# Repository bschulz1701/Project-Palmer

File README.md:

# Project-Palmer
Multiple system designs for golf course turf monitoring project

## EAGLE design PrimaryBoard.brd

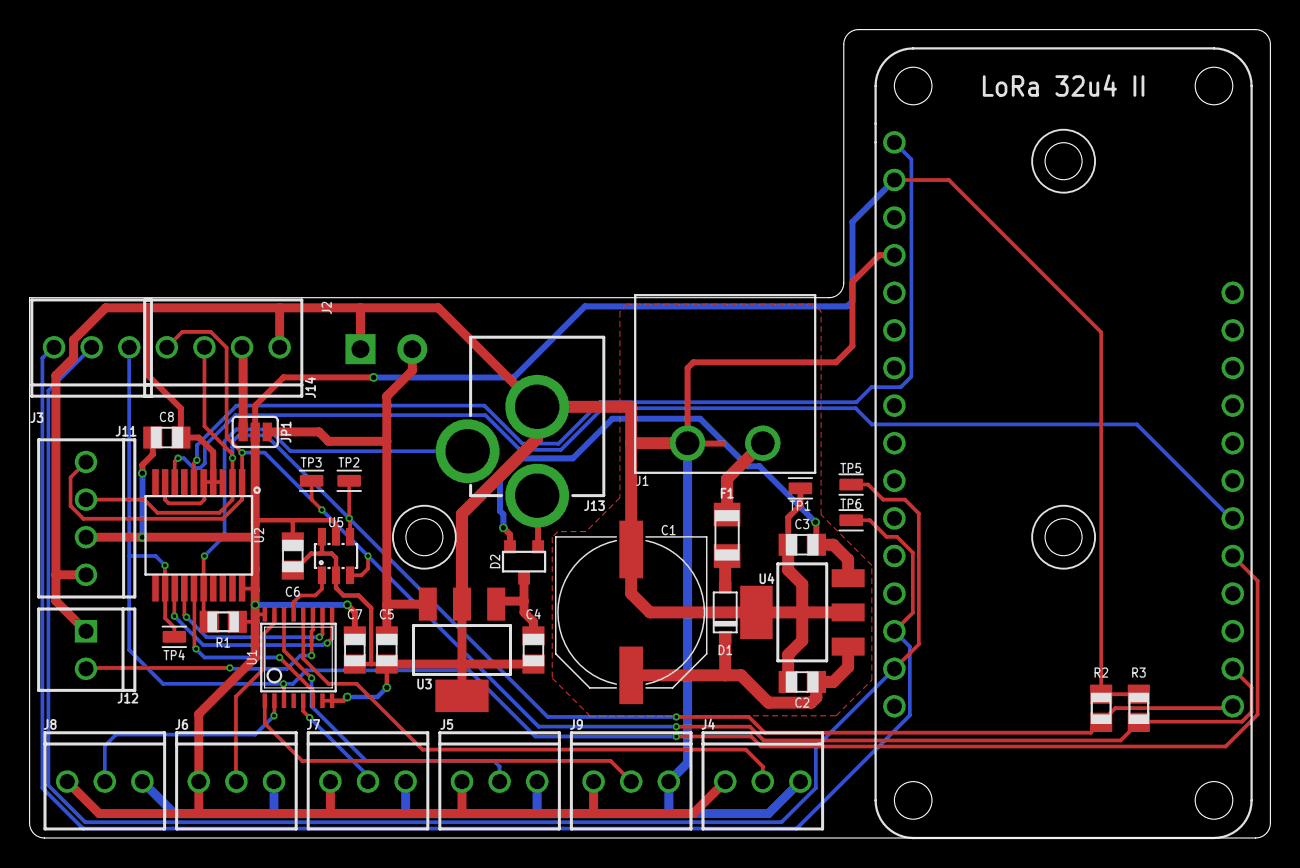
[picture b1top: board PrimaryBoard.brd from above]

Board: 2 copper layers, 83.8 x 54.6 mm, 43 parts (0 on the bottom side), 29 nets.

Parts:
C1: 1000uF; PANASONIC_G
C2: 0.33uF; C0805
C3, C6, C7, C8: 0.1uF; C0805
C4, C5: 1uF; C0805
D1: SOD-123
D2: DIODE_CCSDM40E20LCSOT23; SOT23-3
F1: 50/150mA; 1206
H1, H2, H3: 2_56
J1: 1X02_39532_RIGHT
J2: SCREWTERMINAL-3.5MM-2-NS
J3, J4, J5, J6, J7, J8, J9: CONN_32.54_SCREW; 1X03_SCREW
J10: LORA32U4II
J11, J14: CONN_42.54_SCREW; 1X04_SCREW
J12: 1X02_2.54_SCREWTERM
J13: POWER_JACK; POWER_JACK_PTH
JP1: JUMPER-SMT_3_1-NC_PASTE_SILK; SMT-JUMPER_3_1-NC_PASTE_SILK
R1: 100k; R0805
R2, R3: 10k; R0805
TP1, TP2, TP3, TP4, TP5, TP6: TESTPOINTRCU; TESTPOINT_0603
U1: CD74HC4052PW; TSSOP16
U2: MCP23008SSOP; SSOP20
U3: TC1262-3.3V; SOT223
U4: UA78M05SOT223; SOT223
U5: MCP3421A3; SOT23-6L

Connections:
3V3_CORE: C6.1, C7.1, C8.1, J4.3, J5.3, J6.3, J7.3, J8.3, J9.3, J10.3V3, J11.2, JP1.2, R1.2, R2.2, R3.2, U1.16, U2.20, U5.5
3V3_EXT: J14.3, JP1.1
3V3_MAIN: C5.1, J2.2, JP1.3, U3.3
5V: C3.1, D2.2, U4.3
5V_CORE: C4.1, D2.3, U3.1
5V_EXT: D2.1, J13.PWR
5V_EXT_SENSE: J13.GNDBREAK, R1.1, U2.16
24V_AC: F1.1, J1.2
A0: J4.2, U1.12
A1: J5.2, U1.14
A2: J6.2, U1.15
A3: J12.P1, U1.11
A_COM: U1.13, U5.1
GND: C1.-, C2.2, C3.2, C4.2, C5.2, C6.2, C7.2, C8.2, J1.1, J2.1, J4.1, J5.1, J6.1, J7.1, J8.1, J9.1, J10.GND, J11.1, J12.P2, J13.GND, J14.4, TP1.1, U1.7, U1.8, U2.3, U2.4, U2.5, U2.9, U3.2, U3.4, U4.2, U4.4, U5.2, U5.6
IO_EN: U1.6, U2.15
IO_INT: J10.30, U2.8
unnamed: D1.ANODE, F1.2
ONEWIRE: J3.3, J10.29, TP4.1, U1.3, U2.12
OW0: J9.2, U1.1
OW1: J7.2, U1.5
OW2: J8.2, U1.2
RESET: J10.RST, U2.6
RX: J3.1, J10.20, TP6.1
S0: U1.10, U2.14
S1: U1.9, U2.13
SCL: J10.18, J11.4, J14.1, R3.1, TP3.1, U2.1, U5.3
SDA: J10.19, J11.3, J14.2, R2.1, TP2.1, U2.2, U5.4
TX: J3.2, J10.21, TP5.1
V_RECT: C1.+, C2.1, D1.CAT, U4.1

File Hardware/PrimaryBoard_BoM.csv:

"Qty","Value","Device","Package","Parts","Description","DIGIKEY","DISP","MF","MPN","PROD_ID","SPICEPREFIX","VALUE",
"1","","CONN_022.54_SCREW","1X02_2.54_SCREWTERM","J12","Genaric 2 terminal header","ED10561-ND","","OnShore","OSTVN02A150","","","",
"1","","CONN_023.5MM-NO_SILK","SCREWTERMINAL-3.5MM-2-NS","J2","Genaric 2 terminal header","ED2635-ND","","On Shore Technology","OSTTE020161","CONN-08399","","",
"1","","CONN_0239532_RA","1X02_39532_RIGHT","J1","Genaric 2 terminal header","WM7845-ND","","Molex","0395321002","","","",
"1","","DIODESOD-123","SOD-123","D1","Genaric Diode","1N5819HW-FDICT-ND","","Diodes Incorporated","1N5819HW-7-F","","","",
"3","","MOUNTING_HOLE2_NP","2_56","H1, H2, H3","Genaric Mechanical Mounting Hole","","","","","","","",
"4","0.1uF","C-EU0.1UFC0805","C0805","C3, C6, C7, C8","CAPACITOR, European symbol","399-8000-1-ND","","Kemet","C0805C104M3RACTU","","","",
"1","0.33uF","C-EU0.33UFC0805","C0805","C2","CAPACITOR, European symbol","311-1888-1-ND","","Yageo","CC0805KKX7R9BB334","","","",
"1","1000uF","CPOL-EUG","PANASONIC_G","C1","POLARIZED CAPACITOR, European symbol","P122428CT-ND","","Panasonic","EEE-FT1E102UP","","C","",
"1","100k","R-EU_100KR0805","R0805","R1","RESISTOR, European symbol","311-100KCRCT-ND","","Yageo","RC0805FR-07100KL","","","",
"2","10k","R-EU_10KR0805","R0805","R2, R3","RESISTOR, European symbol","311-10.0KCRCT-ND","","Yageo","RC0805FR-0710KL","","","",
"2","1uF","C-EU1UFC0805","C0805","C4, C5","CAPACITOR, European symbol","311-1456-1-ND","","Yageo","CC0805KKX7R8BB105","","","",
"1","50/150mA","PPTC150MA1206","1206","F1","Bel Fuse PPTC","507-1793-1-ND","","Bell Fuse","0ZCJ0005FF2E","","","50/150mA",
"1","CD74HC4052PW","CD74HC4052PW","TSSOP16","U1","CD74HC4052 - Dual 4x1 Analog Multiplexer/Demultiplexer","296-17619-1-ND","","TI","CD74HC4052PWR","","","",
"7","CONN_32.54_SCREW","CONN_32.54_SCREW","1X03_SCREW","J3, J4, J5, J6, J7, J8, J9","Genaric 3 terminal header","ED10562-ND","","On Shore","OSTVN03A150","","","",
"2","CONN_42.54_SCREW","CONN_42.54_SCREW","1X04_SCREW","J11, J14","Genaric 4 terminal header","ED10563-ND","","On Shore","OSTVN04A150","","","",
"1","DIODE_CCSDM40E20LCSOT23","DIODE_CCSDM40E20LCSOT23","SOT23-3","D2","Dual Diode, Common Cathode","SDM40E20LC-7DICT-ND","","Diodes Incorporated","SDM40E20LC-7","","","",
"1","JUMPER-SMT_3_1-NC_PASTE_SILK","JUMPER-SMT_3_1-NC_PASTE_SILK","SMT-JUMPER_3_1-NC_PASTE_SILK","JP1","Normally closed solder jumper (1 of 2 connections)","","","","","","","",
"1","LORA32U4II","LORA32U4II","LORA32U4II","J10","LoRa 32u4 Mounting Header","","","","","","","",
"1","MCP23008SSOP","MCP23008SSOP","SSOP20","U2","MCP23008 - I2C I/O Expander, 8 bit wtih interrupt and reset","MCP23008T-E/SSCT-ND","","Microchip","MCP23008T-E/SS","","","",
"1","MCP3421A3","MCP3421A3","SOT23-6L","U5","MCP342* - Sigma Delta ADC","MCP3421A3T-E/CHCT-ND","MCP3421","Microchip","MCP3421A3T-E/CH","","","",
"1","POWER_JACK","POWER_JACK","POWER_JACK_PTH","J13","Power Jack Connector","CP-202A-ND","","CUI","PJ-202A","CONN-08197","","",
"1","TC1262-3.3V","TC1262-3.3V","SOT223","U3","TC1262-* - Positive Voltage Regulator","TC1262-3.3VDBCT-ND","TC1262-3.3V","Microchip","TC1262-3.3VDBTR","","","",
"6","TESTPOINTRCU","TESTPOINTRCU","TESTPOINT_0603","TP1, TP2, TP3, TP4, TP5, TP6","","A106145CT-ND","","TE Connectivity","RCU-0C","","","",
"1","UA78M05SOT223","UA78M05SOT223","SOT223","U4","UA78M* - Positive Voltage Regulator","296-17616-1-ND","UA78M05","TI","UA78M05IDCYR","","","",

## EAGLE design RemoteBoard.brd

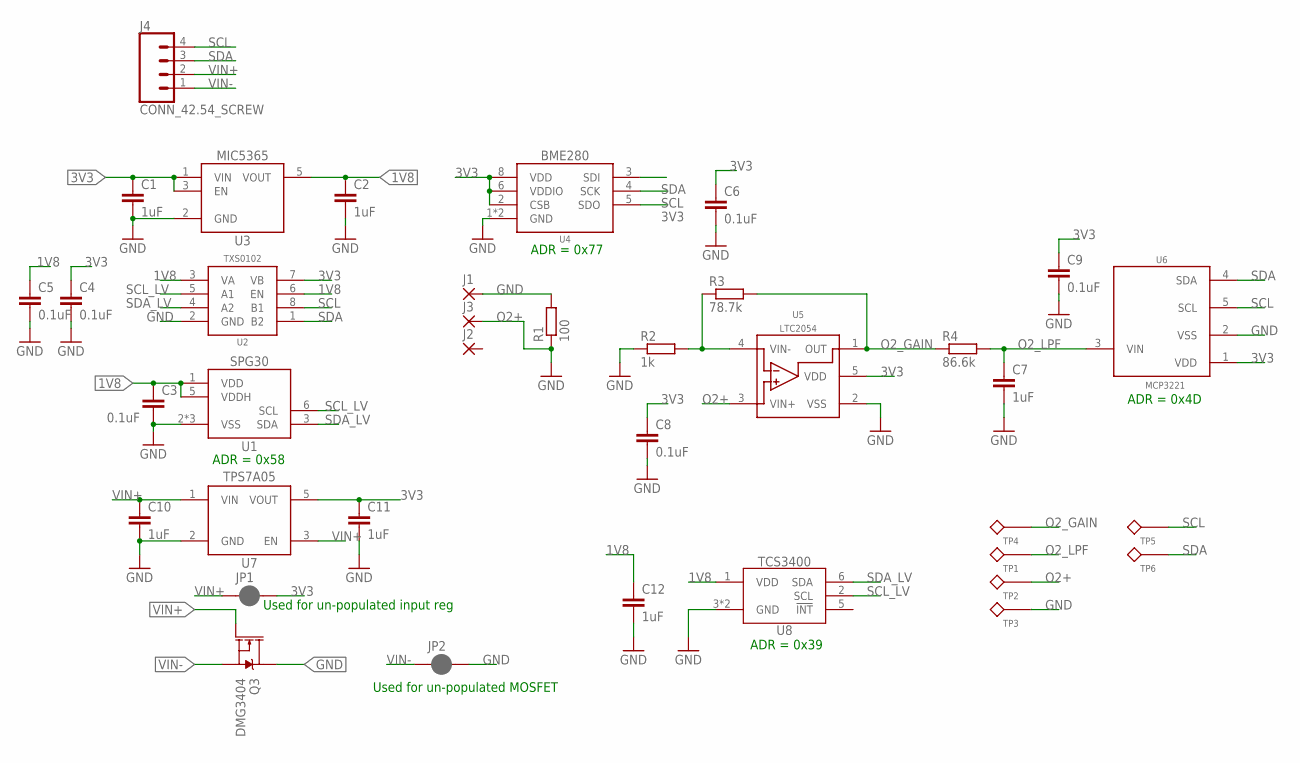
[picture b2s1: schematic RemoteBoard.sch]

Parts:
C1, C2, C7, C10, C11, C12: 1uF; C0805
C3, C4, C5, C6, C8, C9: 0.1uF; C0805
J1, J2, J3: SOCKETS9111_SLOT; SOCKET_S9111-45R_SLOT
J4: CONN_42.54_SCREW; 1X04_SCREW
JP1, JP2: JUMPER-SMT_2_NC_PASTE_SILK; SMT-JUMPER_2_NC_PASTE_SILK
Q3: DMG3404; SOT23-3
R1: 100; R0805
R2: 1k; R0805
R3: 78.7k; R0805
R4: 86.6k; R0805
TP1, TP2, TP3, TP4, TP5, TP6: TESTPOINTRCU; TESTPOINT_0603
U1: SPG30; DFN_6_2.5X2.5
U2: TXS0102DCU; DCU_(R-PDSO-G8)
U3: MIC53651.8SC70; DCK_R-PDSO-G5
U4: BME280
U5: LTC2054; SOT23-5
U6: MCP3221; SOT23-5
U7: TPS7A0533DBV; SOT23-5
U8: TCS3400

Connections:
1V8: C2.1, C3.1, C5.1, C12.1, U1.1 (VDD), U1.5 (VDDH), U2.3 (VA), U2.6 (EN), U3.5 (VOUT), U8.1 (VDD)
3V3: C1.1, C4.1, C6.1, C8.1, C9.1, C11.1, JP1.2, U2.7 (VB), U3.1 (VIN), U3.3 (EN), U4.2 (CSB), U4.5 (SDO), U4.6 (VDDIO), U4.8 (VDD), U5.5 (VDD), U6.1 (VDD), U7.5 (VOUT)
GND: C1.2, C2.2, C3.2, C4.2, C5.2, C6.2, C7.2, C8.2, C9.2, C10.2, C11.2, C12.2, J1.PAD, JP2.2, Q3.3 (D), R1.2, R2.1, TP3.1, U1.2 (VSS), U1.4 (VSS), U1.EP (VSS), U2.2 (GND), U3.2 (GND), U4.1 (GND), U4.7 (GND), U5.2 (VSS), U6.2 (VSS), U7.2 (GND), U8.3 (GND), U8.4 (GND)
unnamed: R2.2, R3.1, U5.4 (VIN-)
O2+: J3.PAD, R1.1, TP2.1, U5.3 (VIN+)
O2_GAIN: R3.2, R4.1, TP4.1, U5.1 (OUT)
O2_LPF: C7.1, R4.2, TP1.1, U6.3 (VIN)
SCL: J4.4, TP5.1, U2.8 (B1), U4.4 (SCK), U6.5 (SCL)
SCL_LV: U1.6 (SCL), U2.5 (A1), U8.2 (SCL)
SDA: J4.3, TP6.1, U2.1 (B2), U4.3 (SDI), U6.4 (SDA)
SDA_LV: U1.3 (SDA), U2.4 (A2), U8.6 (SDA)
VIN+: C10.1, J4.2, JP1.1, Q3.1 (G), U7.1 (VIN), U7.3 (EN)
VIN-: J4.1, JP2.1, Q3.2 (S)

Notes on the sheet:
Used for un-populated MOSFET
Used for un-populated input reg
ADR = 0x4D
ADR = 0x58
ADR = 0x77
ADR = 0x39

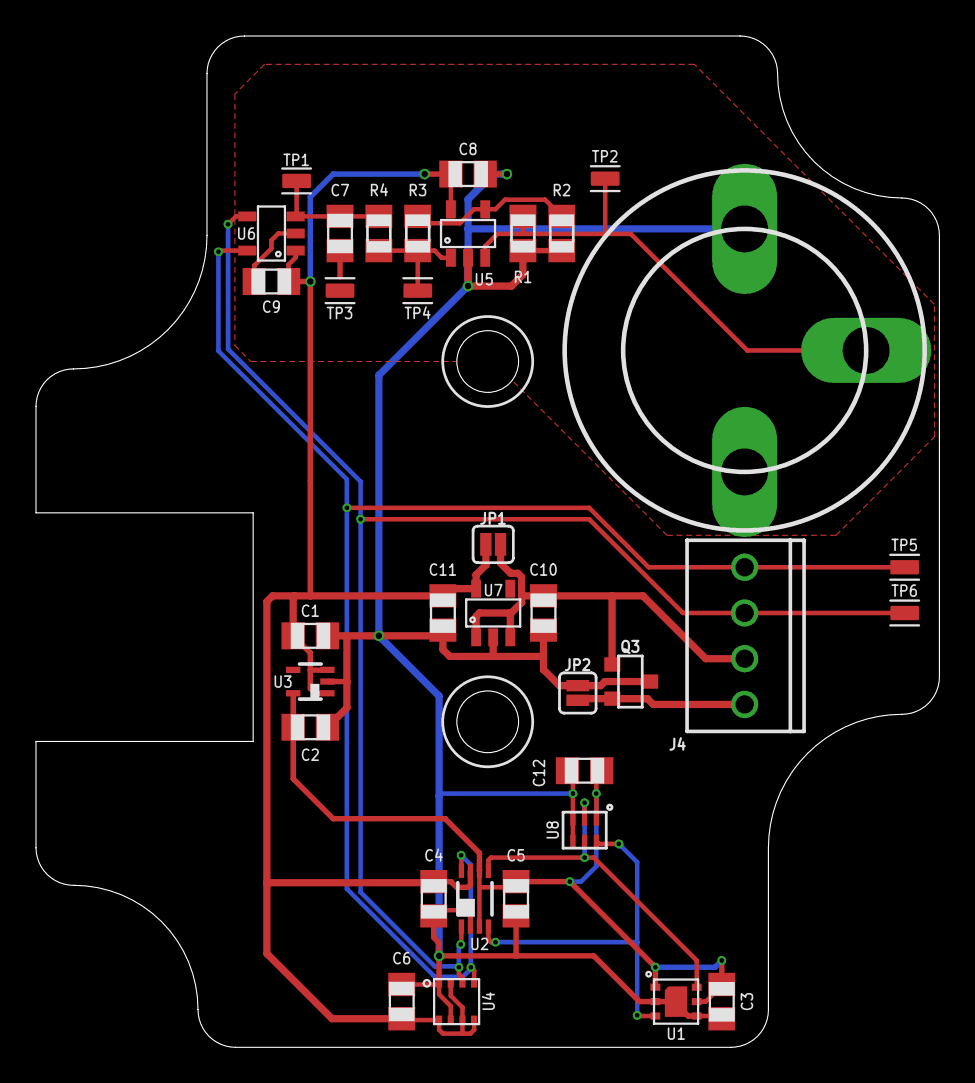
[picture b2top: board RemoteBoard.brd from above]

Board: 2 copper layers, 50.2 x 56.2 mm, 37 parts (0 on the bottom side), 13 nets.

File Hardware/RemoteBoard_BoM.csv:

"Qty","Value","Device","Package","Parts","Description","DIGIKEY","DISP","MF","MOUSER","MPN","VALUE",
"6","0.1uF","C-EU0.1UFC0805","C0805","C3, C4, C5, C6, C8, C9","CAPACITOR, European symbol","399-8000-1-ND","","Kemet","","C0805C104M3RACTU","",
"1","100","R-EU_100R0805","R0805","R1","RESISTOR, European symbol","311-100CRCT-ND","","Yageo","","RC0805FR-07100RL","",
"1","1k","R-EU_1KR0805","R0805","R2","RESISTOR, European symbol","311-1.00KCRCT-ND","","Yageo","","RC0805FR-071KL","",
"6","1uF","C-EU1UFC0805","C0805","C1, C2, C7, C10, C11, C12","CAPACITOR, European symbol","311-1456-1-ND","","Yageo","","CC0805KKX7R8BB105","",
"1","78.7k","R-EU_78.7KR0805","R0805","R3","RESISTOR, European symbol","311-78.7KCRCT-ND","","Yageo","","RC0805FR-0778K7L","",
"1","86.6k","R-EU_86.6KR0805","R0805","R4","RESISTOR, European symbol","311-86.6KCRCT-ND","","Yageo","","RC0805FR-0786K6L","",
"1","BME280","BME280","BME280","U4","BME280 - Combined Digital Humidity and Pressure Sensor","828-1063-1-ND","BME280","Bosch","","BME280","",
"1","CONN_42.54_SCREW","CONN_42.54_SCREW","1X04_SCREW","J4","Genaric 4 terminal header","ED10563-ND","","On Shore","","OSTVN04A150","",
"1","DMG3404","MOSFET-NCH-DMG3404L","SOT23-3","Q3","N-channel MOSFETs","DMG3404L-7DICT-ND","","Diodes Incorporated","","DMG3404L-7","DMG3404",
"2","JUMPER-SMT_2_NC_PASTE_SILK","JUMPER-SMT_2_NC_PASTE_SILK","SMT-JUMPER_2_NC_PASTE_SILK","JP1, JP2","Normally closed solder jumper","","","","","","",
"1","LTC2054","LTC2054","SOT23-5","U5","LTC2054 -Single Micropower Zero Drift Op-Amp","LTC2054HS5#TRMPBFCT-ND","LTC2054","LT","","LTC2054HS5#TRMPBF","",
"1","MCP3221","MCP3221","SOT23-5","U6","MCP342* - SAR ADC","MCP3221A5T-I/OTCT-ND","MCP3221","TI","","MCP3221A5T-I/OT","",
"1","MIC53651.8SC70","MIC53651.8SC70","DCK_R-PDSO-G5","U3","MIC5365-* - Low Power, High Performance, Linear Regulator","576-3181-1-ND","","Microchip","","MIC5365-1.8YC5-TR","",
"3","SOCKETS9111_SLOT","SOCKETS9111_SLOT","SOCKET_S9111-45R_SLOT","J1, J2, J3","Generic Board Socket","952-3660-1-ND","","Harwin","","S9111-45R","",
"1","SPG30","SPG30","DFN_6_2.5X2.5","U1","SGP30 - Multi-pixel Gas Sensor (TVOC, CO2EQ)","1649-1084-1-ND","","Sensirion","","SGP30-2.5K","",
"1","TCS3400","TCS3400","TCS3400","U8","TCS3400 - Ambient Multi-Band Light Sensor with I2C Interface","TCS34003FNMCT-ND","","AMS","","TCS34003FNM","",
"6","TESTPOINTRCU","TESTPOINTRCU","TESTPOINT_0603","TP1, TP2, TP3, TP4, TP5, TP6","","A106145CT-ND","","TE Connectivity","","RCU-0C","",
"1","TPS7A0533DBV","TPS7A0533DBV","SOT23-5","U7","TPS7A05* - Ultra Low Power Low Dropout Linear Regulator","296-50256-1-ND","","TI","595-TPS7A0533PDBVR","TPS7A0533PDBVR","",
"1","TXS0102DCU","TXS0102DCU","DCU_(R-PDSO-G8)","U2","TXS0102 - 2 Channel Bidirectional Voltage Level Translator","296-21931-1-ND","","TI","","TXS0102DCUR","",

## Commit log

2019-10-11 Added license
2019-10-11 Added git LFS support
2019-10-11 Added rectifier design pdf
2019-10-15 Added spectral response data
    Added extracted spectral response data to compare TCS3200 and TCS3400
2019-10-16 Preliminary Primary Board CAD
    Preliminary schematic entry and board layout
2019-10-17 Beginning schematic capture for Remote Board
2019-10-18 Minor updates and cleanup for primary board
2019-10-18 Continued schematic capture for remote board, layout begin
    Schematic for remote board complete except for TCS3400, significant layout progress
2019-10-21 Minor updates to Primary and Remote
    Cleaned up/added silkscreen, added test points to both boards
2019-10-22 Added LoRa 32u4 updated dimensions
2019-10-24 Added matlab data O2 sensor test analysis
2019-10-24 Minor cleanup/fixes to boards, generated gerbers
    Minor changes to boards, primarily cleanup and generated gerbers for fab, ready for review
2019-10-25 Minor updates, part vals
    Changed 1x7 connector on Primary board to 1x4 and 1x3 because 1x7 0.1" screw terminals are made of Corinthian Leather apparently, also updated part values and BoM vals
2019-10-25 Generated BoM for both boards
2019-11-13 Updated repo folder structure
2019-11-13 Added BETA code for Palmer system
    Added individual test components (in BETA but lacking full feature set) and combined demo program, in BETA with full preliminary feature set.
    Migration from Margay to LoRa 32u4 required
2019-11-13 Fixed #ifdef in combo demo
2019-11-20 Added LoRa node software
2019-11-20 Cleanup/Minor updates to logging code
    Added comment descriptor, updated ifdef system to allow for echoing LoRa transmission to serial monitor, changed the format of serial print to be echo of LoRa string instead of new line style, change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
2019-11-21 Fixed LoRa config issue, added support for hardware serial output
    Added support for hardware serial output to support use of openlog, fixed LoRa configuration issue
2019-11-23 Adjusted LFS attributes for mechanical parts
2019-11-23 Added designs for soil moisture holders
    Added mechanical designs for soil moisture probe holders (for 3D printing)
2019-11-26 Added blink and period update
2019-12-09 Added drill guide PDF for box
2020-03-13 Added port of software to Particle Boron
2020-04-01 Changed/removed git lfs
2020-04-01 Updated folder structure, readme, and git lfs issues
    Updated PDFs and other files to be free of git lfs, updated readme, added main data sheets
2020-04-01 Removed erroneous GND symbol

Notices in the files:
parts and their libraries:
SparkFun-Jumpers: Licensing: Creative Commons ShareAlike 4.0 International - https://creativecommons.org/licenses/by-sa/4.0
